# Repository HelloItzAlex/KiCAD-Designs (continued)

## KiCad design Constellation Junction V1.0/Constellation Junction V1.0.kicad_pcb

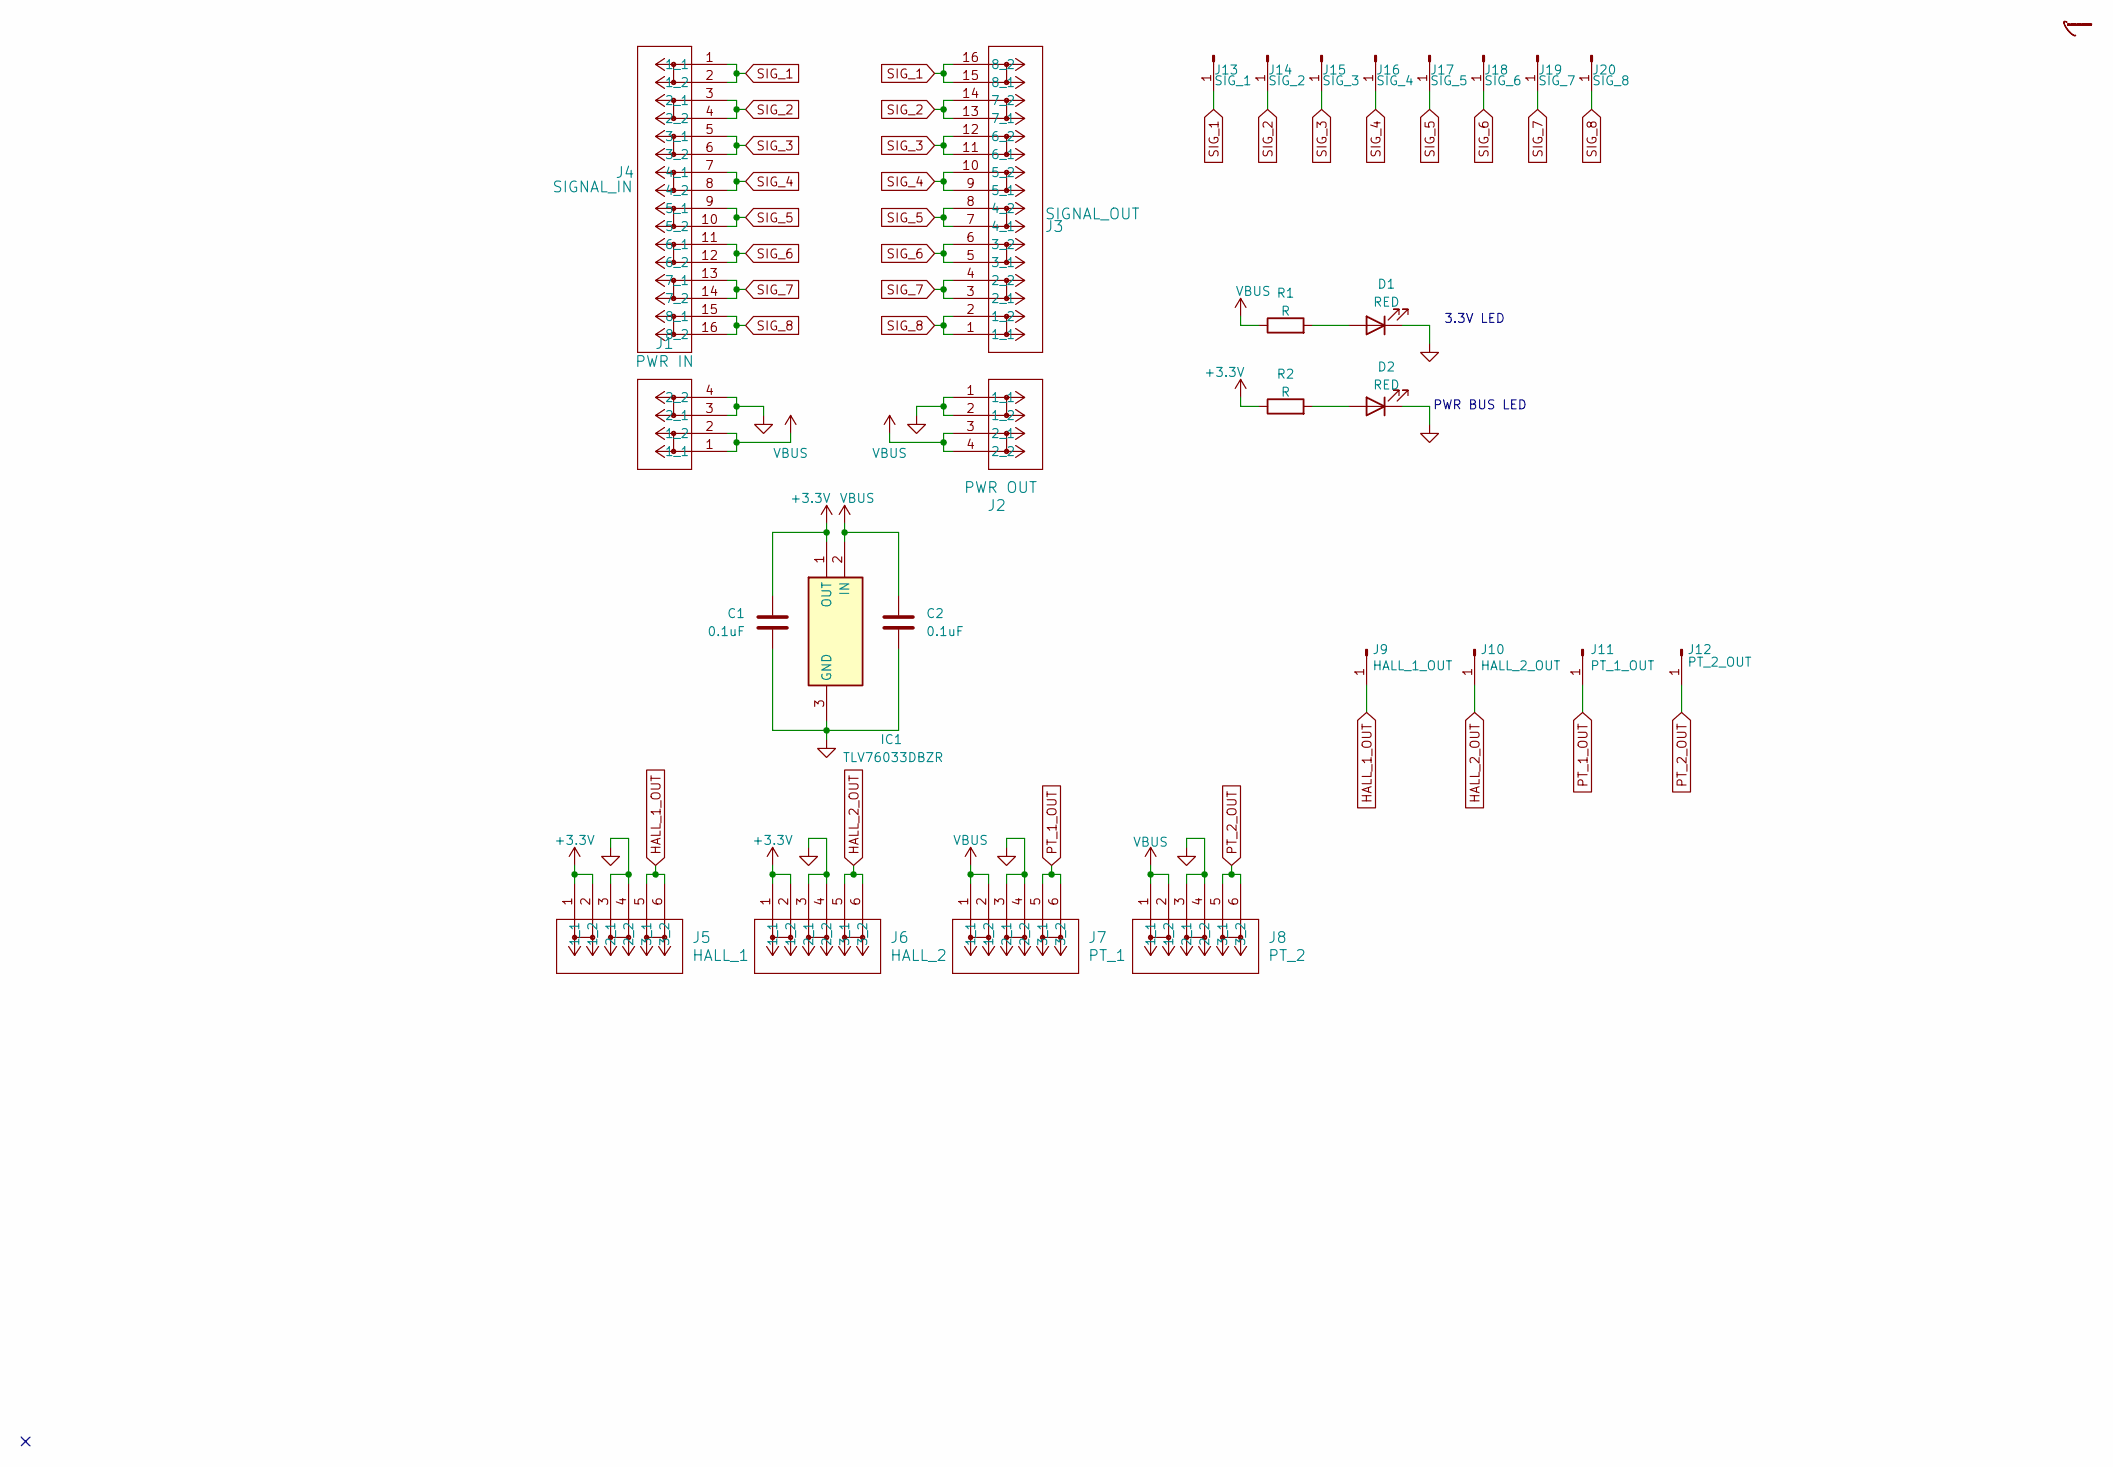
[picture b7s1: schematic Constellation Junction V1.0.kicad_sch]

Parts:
C1, C2: 0.1uF; C_0805_2012Metric
D1, D2: RED; LED_0805_2012Metric
IC1: TLV76033DBZR; SOT95P237X112-3N; Mouser Part Number 595-TLV76033DBZR
J1: PWR IN; CONN2_2601-1102_WAG
J2: PWR OUT; CONN2_2601-1102_WAG
J3: SIGNAL_OUT; CONN8_2601-1108_WAG
J4: SIGNAL_IN; CONN8_2601-1108_WAG
J5: HALL_1; CONN3_2601-1103_WAG
J6: HALL_2; CONN3_2601-1103_WAG
J7: PT_1; CONN3_2601-1103_WAG
J8: PT_2; CONN3_2601-1103_WAG
J9: HALL_1_OUT; PinSocket_1x01_P2.54mm_Vertical
J10: HALL_2_OUT; PinSocket_1x01_P2.54mm_Vertical
J11: PT_1_OUT; PinSocket_1x01_P2.54mm_Vertical
J12: PT_2_OUT; PinSocket_1x01_P2.54mm_Vertical
J13: SIG_1; PinSocket_1x01_P2.54mm_Vertical
J14: SIG_2; PinSocket_1x01_P2.54mm_Vertical
J15: SIG_3; PinSocket_1x01_P2.54mm_Vertical
J16: SIG_4; PinSocket_1x01_P2.54mm_Vertical
J17: SIG_5; PinSocket_1x01_P2.54mm_Vertical
J18: SIG_6; PinSocket_1x01_P2.54mm_Vertical
J19: SIG_7; PinSocket_1x01_P2.54mm_Vertical
J20: SIG_8; PinSocket_1x01_P2.54mm_Vertical
R1, R2: R; R_0805_2012Metric

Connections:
+3.3V: C1.1, IC1.1 (OUT), J5.1 (1_1), J5.2 (1_2), J6.1 (1_1), J6.2 (1_2), R2.1
GND: C1.2, C2.2, D1.1 (K), D2.1 (K), IC1.3 (GND), J1.3 (2_1), J1.4 (2_2), J2.1 (1_1), J2.2 (1_2), J5.3 (2_1), J5.4 (2_2), J6.3 (2_1), J6.4 (2_2), J7.3 (2_1), J7.4 (2_2), J8.3 (2_1), J8.4 (2_2)
HALL_1_OUT: J5.5 (3_1), J5.6 (3_2), J9.1
HALL_2_OUT: J6.5 (3_1), J6.6 (3_2), J10.1
unnamed: D1.2 (A), R1.2
unnamed: D2.2 (A), R2.2
PT_1_OUT: J7.5 (3_1), J7.6 (3_2), J11.1
PT_2_OUT: J8.5 (3_1), J8.6 (3_2), J12.1
SIG_1: J3.15 (8_1), J3.16 (8_2), J4.1 (1_1), J4.2 (1_2), J13.1
SIG_2: J3.13 (7_1), J3.14 (7_2), J4.3 (2_1), J4.4 (2_2), J14.1
SIG_3: J3.11 (6_1), J3.12 (6_2), J4.5 (3_1), J4.6 (3_2), J15.1
SIG_4: J3.9 (5_1), J3.10 (5_2), J4.7 (4_1), J4.8 (4_2), J16.1
SIG_5: J3.7 (4_1), J3.8 (4_2), J4.9 (5_1), J4.10 (5_2), J17.1
SIG_6: J3.5 (3_1), J3.6 (3_2), J4.11 (6_1), J4.12 (6_2), J18.1
SIG_7: J3.3 (2_1), J3.4 (2_2), J4.13 (7_1), J4.14 (7_2), J19.1
SIG_8: J3.1 (1_1), J3.2 (1_2), J4.15 (8_1), J4.16 (8_2), J20.1
VBUS: C2.1, IC1.2 (IN), J1.1 (1_1), J1.2 (1_2), J2.3 (2_1), J2.4 (2_2), J7.1 (1_1), J7.2 (1_2), J8.1 (1_1), J8.2 (1_2), R1.1

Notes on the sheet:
PWR BUS LED
3.3V LED

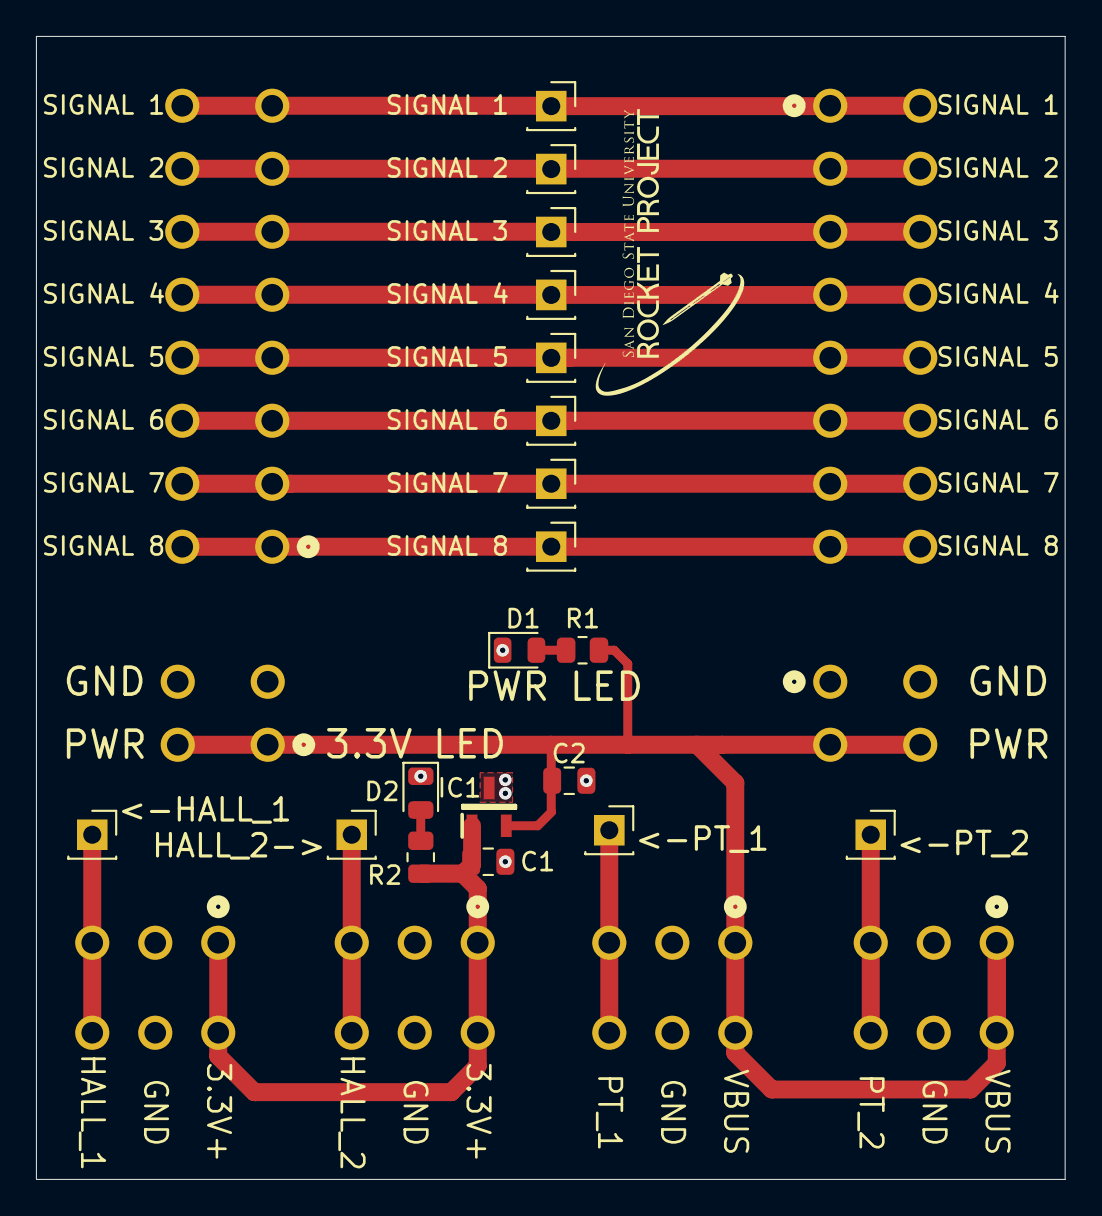
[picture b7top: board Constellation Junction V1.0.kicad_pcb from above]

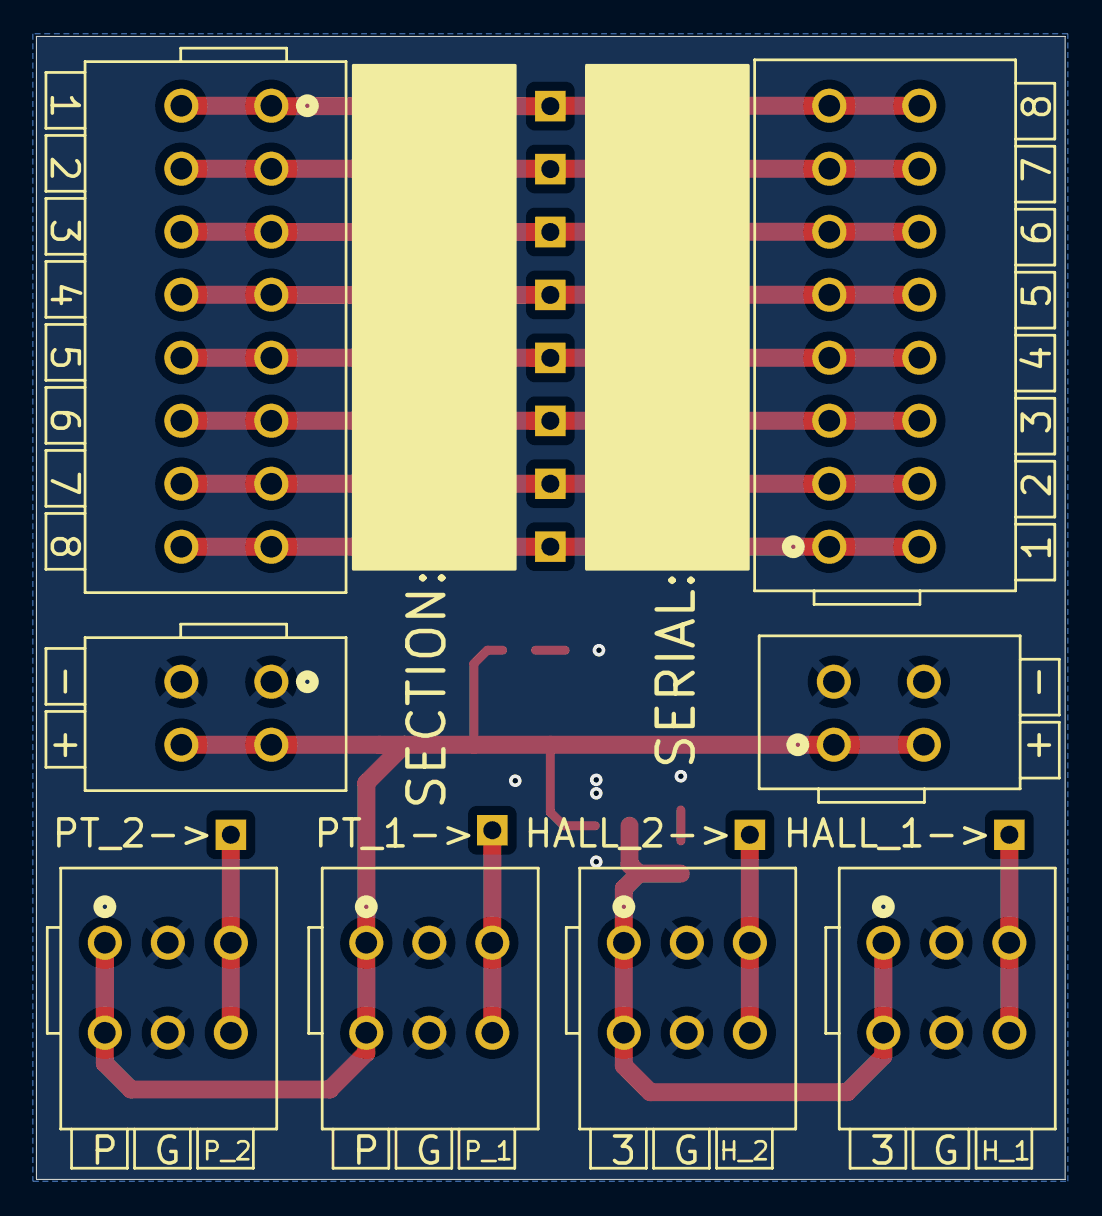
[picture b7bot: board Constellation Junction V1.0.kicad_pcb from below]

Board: 2 copper layers, 57.1 x 63.5 mm, 27 parts (8 on the bottom side), 17 nets.
